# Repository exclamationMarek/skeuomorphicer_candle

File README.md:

# Skeuomorphicer Candle

A more skeuomorphic LED candle, one that you turn on with a flame, and off with a blow, like a real candle!
Super simple design with no microcontrollers, op-amps nor any other integrated circuits. Just one transistor, one thermistor and a couple of passives.

As seen on youtube, here: [https://www.youtube.com/watch?v=r8O8MNvkZiY](https://www.youtube.com/watch?v=r8O8MNvkZiY)

# How it works

* Heating the NTC thermistor makes its resistance drop, which increases the voltage on the MOSFET gate and turns on the bulb
* The current limiting R2 resistor gets hot
* The PCB is carefully designed to thermally connect R2 to the NTC
* Heat from R2 makes the NTC hot, so it stays hot even when the flame is removed
* This keeps the candle on
* Once you blow on the PCB, the heat is removed, breaking the cycle and turning off the light
* Yes, the schematic looks like a candle

* The current limiting (and heat producing) resistor is doubled, to surround the NTC on both sides
* They also share an electrical connection with the NTC - the VCC node (on top)
* That VCC copper connection is used to transfer heat from the resistors to the NTC
* But also, is wide and exposed to being blown at
* This is a finicky design challenge that required iterative fine tuning
* The current implementation works best with about 0.1W (total) dissipated on the heating resistors, which keeps the NTC at about 55°C
* Testd on a 1.0mm 2-layer PCB with 35um copper foil. Tested with black solder mask (it might make a difference?)

Note that this is the simplified schematic that omits the power supply. In real application, the varying voltage of batteries causes the circuit to be unreliable. With a full battery, the NTC runs too hot, making the candle difficult to blow out, and with a low battery it runs too cool, turning itself off unprompted. To fix this, the recommended design adds a voltage regulator (boost converter) to keep VCC stable and the candle reliable.

# PCB design available in 4 variants:
## [Minimal](Skeuomorphic_candle_minimal)
* Designed for 1.5V mini light bulb and 2xAA batteries
* Very low component count
* Does not work with LEDs!
* No ICs. Just 1 NMOS, 1 NTC and some resistors
* If you want the simplest skeuomorphicer candle, use this PCB.
* Alternatively, use with external 3.3V regulated supply

## [Basic - recommended](Skeuomorphic_candle_basic)
* Works great with a mini light bulb and OK-ish with LEDs
* Supports various batteries
* Low component count, but requires power regulator IC
* If you want to make a resonably well working skeuomorphicer candle, use this PCB

## [Custom](Skeuomorphic_candle_custom)
* PCB with extra footprints for implementation flexibility
* Can be configured as either the "Minimal" or "Basic" variant
* Can be configured as bulb + LEDs
* LED brightness can be adjusted, while maintaining reliable flame detection
* Has test points
* If you want to experiment with the design, use this PCB

## [Digital](Skeuomorphic_candle_digital)
* EWWWW digital microcontroller!
* 32bits?! For like one 'if' statement?!
* 2KB of RAM?! You can fly to the bloody moon on 2KB of RAM!
* If you're one of those futuristic cyberpunk chooms, use this PCB. I will try not to cry.

Detailed configuration and assembly instructions are in each PCB variant folder.

# License
This project is published under the [Creative Commons Attribution-NonCommercial 4.0 License](https://creativecommons.org/licenses/by-nc/4.0/deed.en)

Full text in license.txt

A commertial use license may be provided upon request

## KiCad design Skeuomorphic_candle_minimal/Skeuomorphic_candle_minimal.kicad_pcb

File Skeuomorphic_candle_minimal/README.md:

# Minimal Skeuomorphicer Candle
Does not work great, but uses very few parts

# UNTESTED!
As of releasing this repo, this PCB design is NOT TESTED. It might be all wrong.

# Part list (light bulb configuration)
* 1x 1.5V miniature tungsten bulb. Should draw about 100-130mA at 1.5V
* 1x SI2302 N-MOS (or similar)
* 1x 100k NTC in 0603 package
* 2x 33R resistors in 0603 package
* 1x 6.8k resistor in 0603 package
* 1x battery holder for 2xAA
* 2x AA battery (NiMH rechargable works great)

# Assembly manual (light bulb configuration)
* Populate all components as listed in the schematic
* Find a value of R1 that makes candle work well. REDUCE if hard to blow out, INCREASE if does not stay on
* Note that as the batteries are discharged, the threshold will shift, making it more likely that the candle does not stay on
* Therefore, tune R1 with full batteries, and make it so that it is barely possible to blow out the candle
* Supply from 2xAA batteries

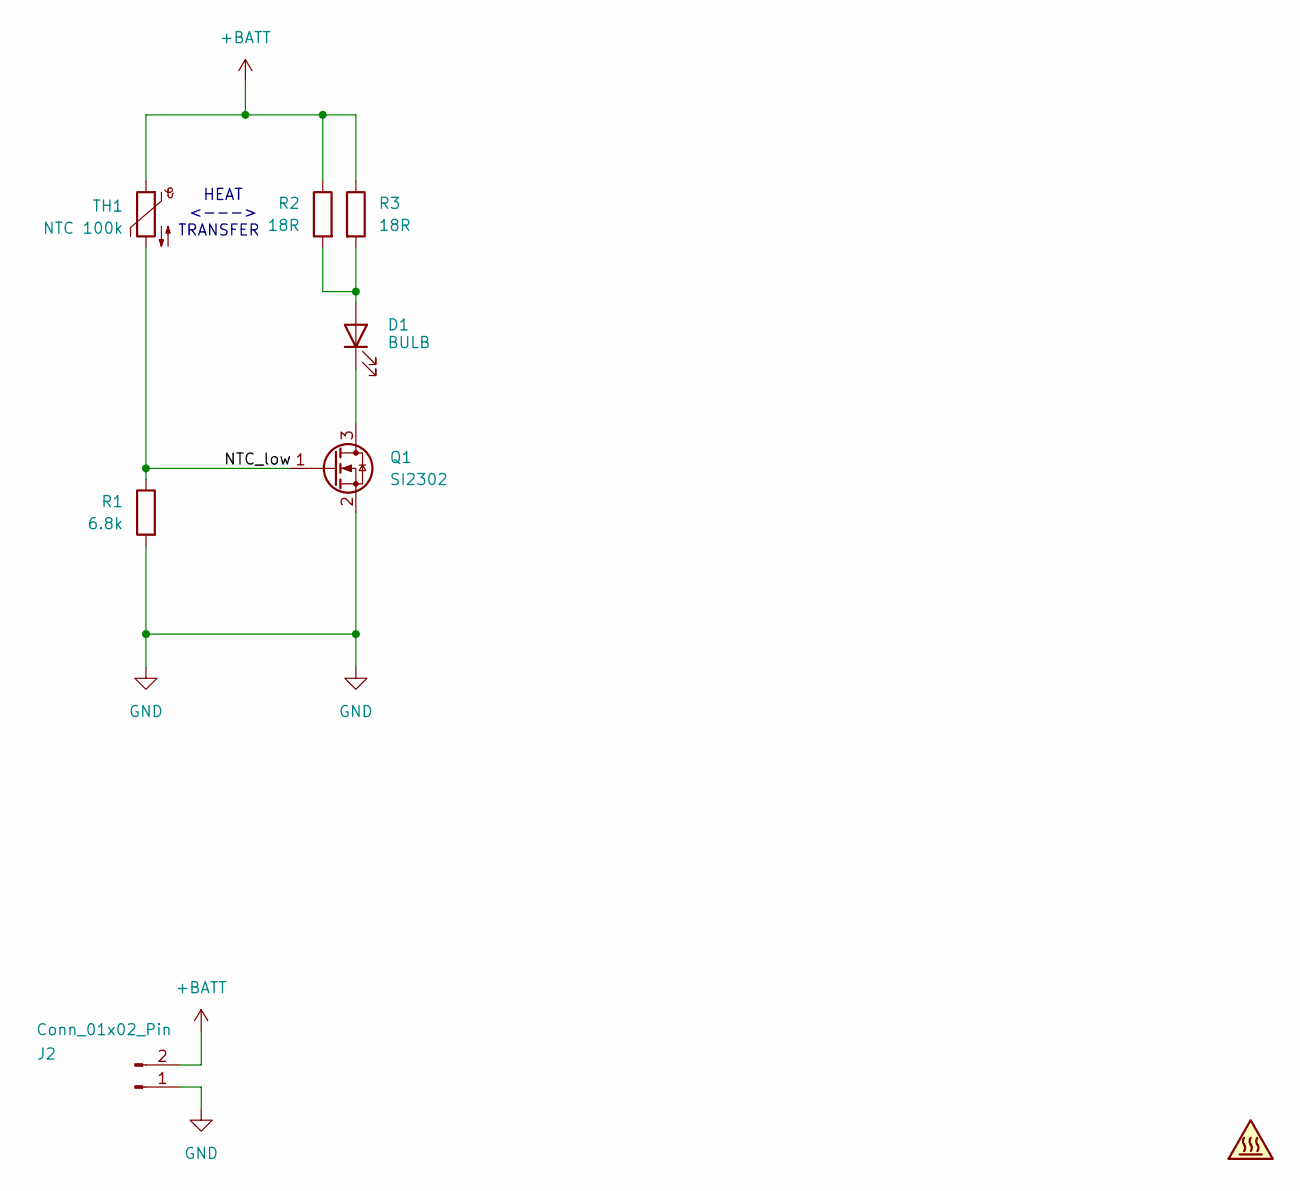
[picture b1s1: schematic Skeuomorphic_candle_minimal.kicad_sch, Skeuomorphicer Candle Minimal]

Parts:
D1: BULB; Mini_bulb_flat
J2: Conn_01x02_Pin; PinHeader_1x02_P2.54mm_Vertical
LOGO1: Logo; Skeuomorphicer_candle_logo
Q1: SI2302; SOT-23-handsoldering-smaller
R1: 6.8k; R_0603_1608Metric_Pad0.98x0.95mm_HandSolder
R2, R3: 18R; R_0603_1608Metric_Pad0.98x0.95mm_HandSolder
TH1: NTC 100k; R_0603_1608Metric_Pad0.98x0.95mm_HandSolder

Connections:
+BATT: J2.2, R2.1, R3.1, TH1.1
/NTC_low: Q1.1 (G), R1.1, TH1.2
GND: J2.1, Q1.2 (S), R1.2
unnamed: D1.2 (A), R2.2, R3.2
unnamed: D1.1 (K), Q1.3 (D)

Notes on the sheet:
HEAT <---> TRANSFER

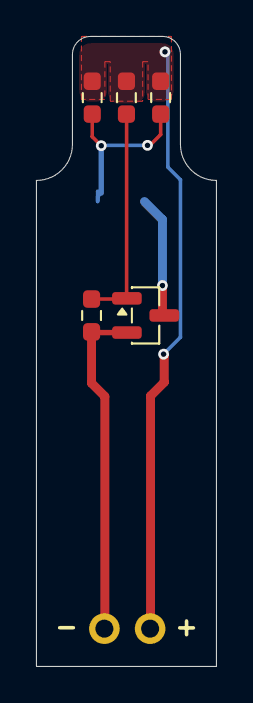
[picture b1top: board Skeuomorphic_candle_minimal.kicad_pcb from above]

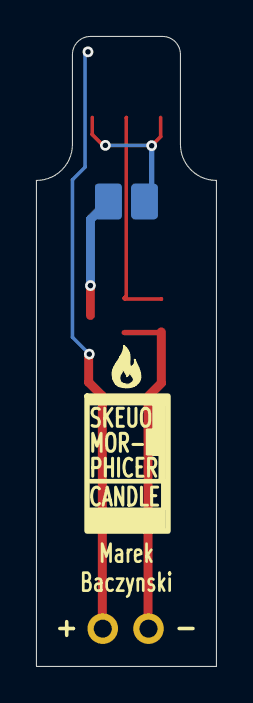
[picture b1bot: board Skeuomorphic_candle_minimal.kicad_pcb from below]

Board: 2 copper layers, 10.0 x 35.0 mm, 8 parts (2 on the bottom side), 5 nets.

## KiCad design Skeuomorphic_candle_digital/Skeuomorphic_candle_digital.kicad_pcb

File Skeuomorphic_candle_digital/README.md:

# Digital Skeuomorphicer Candle
For when you just have to put code into everything

# UNTESTED!
As of releasing this repo, this PCB design is NOT TESTED. It might be all wrong.

# Part list
* CH32V003J4M6 microcontroller in SOP-8 package
* 100k NTC in 0603
* SI2302 NMOS (or similar)
* 1uF capacitor in 0603 for the MCU
* 3V miniature tungsten bulb, or 2x 2835 LEDs
* Some 0603 resistors
* Optionally some 0603 LEDs
* 3xAA or 3xAAA battery holder or 1x LiPo battery

# Firmware
Firmware for the Digital Skeuomorphicer Candle is comming soon. Probably.

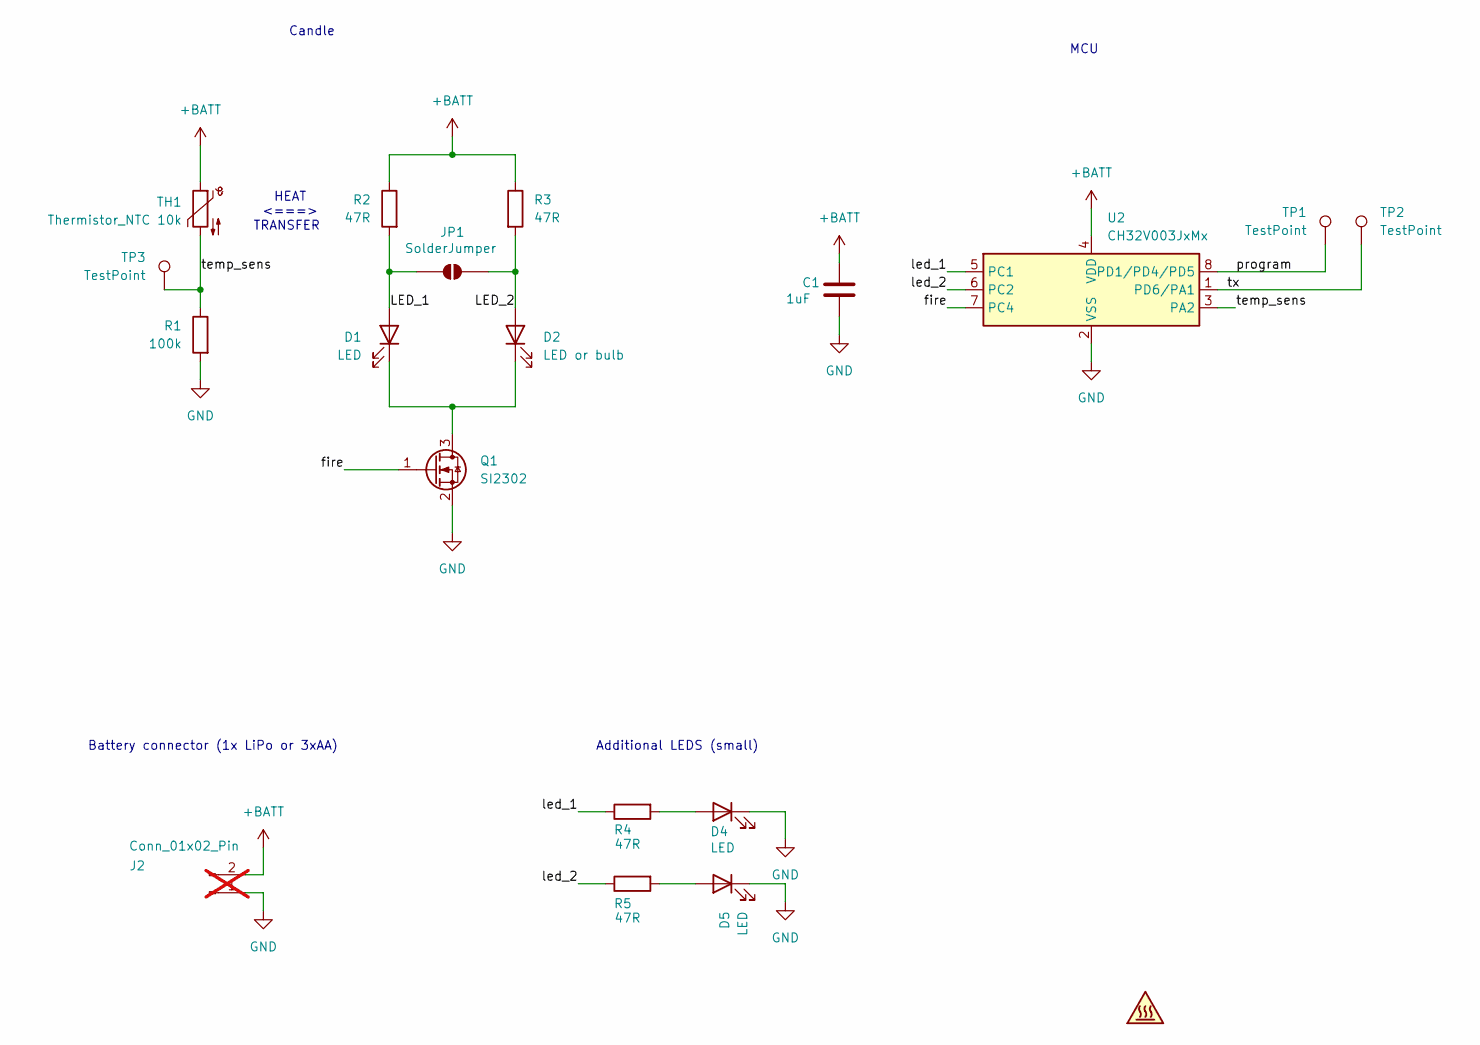
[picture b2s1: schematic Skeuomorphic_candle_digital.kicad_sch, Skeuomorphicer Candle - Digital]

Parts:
C1: 1uF; C_0603_1608Metric_Pad1.08x0.95mm_HandSolder
D1: LED; LED_PLCC_2835_Handsoldering
D2: LED or bulb; LED_PLCC_2835_Handsoldering
D4, D5: LED; LED_0603_1608Metric_Pad1.05x0.95mm_HandSolder
J2: Conn_01x02_Pin; PinHeader_1x02_P2.54mm_Vertical; not fitted
JP1: SolderJumper; SolderJumper-2_P1.3mm_Open_RoundedPad1.0x1.5mm
LOGO1: Logo; Skeuomorphicer_candle_logo
Q1: SI2302; SOT-23-handsoldering-smaller
R1: 100k; R_0603_1608Metric_Pad0.98x0.95mm_HandSolder
R2, R3, R4, R5: 47R; R_0603_1608Metric_Pad0.98x0.95mm_HandSolder
TH1: Thermistor_NTC 10k; R_0603_1608Metric_Pad0.98x0.95mm_HandSolder
TP1, TP2, TP3: TestPoint; TestPoint_Pad_D1.0mm
U2: CH32V003JxMx; JEITA_SOIC-8_3.9x4.9mm_P1.27mm

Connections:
+BATT: C1.1, J2.2, R2.1, R3.1, TH1.1, U2.4 (VDD)
/LED_1: D1.2 (A), JP1.1 (A), R2.2
/LED_2: D2.2 (A), JP1.2 (B), R3.2
/fire: Q1.1 (G), U2.7 (PC4)
/led_1: R4.1, U2.5 (PC1)
/led_2: R5.1, U2.6 (PC2)
/program: TP1.1 (1_1), U2.8 (PD1/PD4/PD5)
/temp_sens: R1.1, TH1.2, TP3.1 (1_1), U2.3 (PA2)
/tx: TP2.1 (1_1), U2.1 (PD6/PA1)
GND: C1.2, D4.1 (K), D5.1 (K), J2.1, Q1.2 (S), R1.2, U2.2 (VSS)
unnamed: D1.1 (K), D2.1 (K), Q1.3 (D)
unnamed: D4.2 (A), R4.2
unnamed: D5.2 (A), R5.2

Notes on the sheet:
MCU
Battery connector (1x LiPo or 3xAA)
HEAT <===> TRANSFER
Additional LEDS (small)
Candle

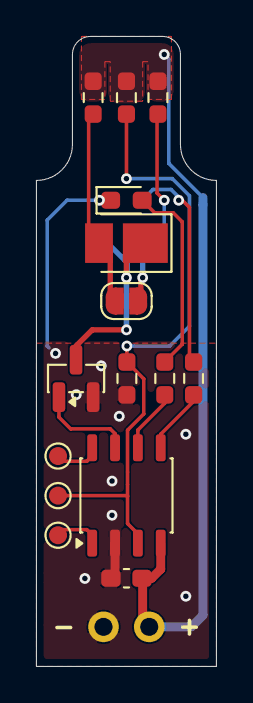
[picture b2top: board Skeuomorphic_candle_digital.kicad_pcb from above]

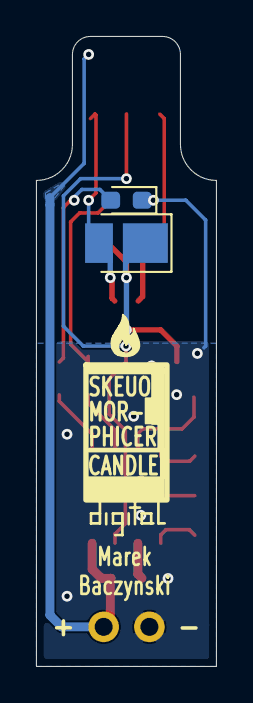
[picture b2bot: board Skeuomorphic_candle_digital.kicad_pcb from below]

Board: 2 copper layers, 10.0 x 35.0 mm, 19 parts (3 on the bottom side), 13 nets.

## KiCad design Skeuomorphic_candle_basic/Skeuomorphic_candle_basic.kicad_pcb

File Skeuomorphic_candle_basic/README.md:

# Basic Skeuomorphicer Candle
Most recommended design

# UNTESTED!
As of releasing this repo, this PCB design is NOT TESTED. It might be all wrong.

# Part list (light bulb configuration)
* 1x 1.5V miniature tungsten bulb. Should draw about 100-130mA at 1.5V
* 1x SI2302 N-MOS (or similar)
* 1x ETA1061V33 boost converter with 3.3V output
* 1x 2.2uH inductor in 1008 package
* 2x 4.7uF capacitors in 0603 package
* 1x 100k NTC in 0603 package
* 2x 33R resistors in 0603 package
* 1x 6.8k resistor in 0603 package
* 1x battery holder for 2xAA
* 2x AA battery (NiMH rechargable works great)

# Assembly manual (light bulb configuration)
* Bridge Jumper JP1
* Skip D1
* Place 1.5V bulb on D2
* Use 3v3 out regulator for U1
* Populate all other components as listed in the schematic
* Find a value of R1 that makes candle work well. REDUCE if hard to blow out, INCREASE if does not stay on
* Supply from 2xAA or 2xAAA batteries

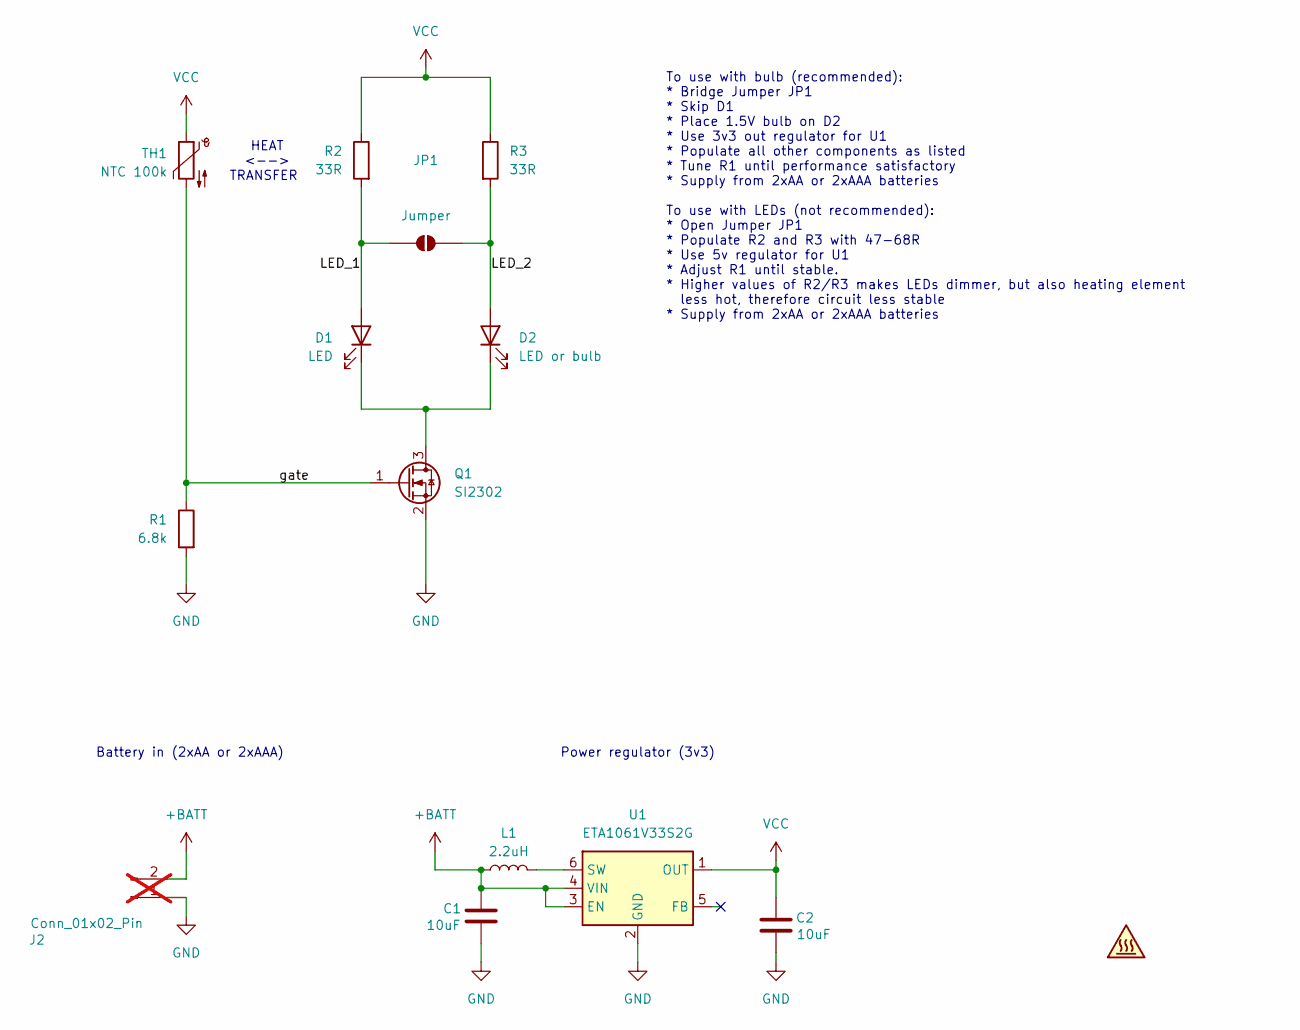
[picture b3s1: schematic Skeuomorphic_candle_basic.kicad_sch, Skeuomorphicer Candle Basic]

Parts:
C1, C2: 10uF; C_0603_1608Metric_Pad1.08x0.95mm_HandSolder
D1: LED; LED_PLCC_2835_Handsoldering
D2: LED or bulb; LED_PLCC_2835_Handsoldering
J2: Conn_01x02_Pin; PinHeader_1x02_P2.54mm_Vertical; not fitted
JP1: Jumper; SolderJumper-2_P1.3mm_Open_RoundedPad1.0x1.5mm
L1: 2.2uH; L_1008_2520Metric_Pad1.43x2.20mm_HandSolder; MPN WIP252012P-2R2ML
LOGO1: Logo; Skeuomorphicer_candle_logo
Q1: SI2302; SOT-23-handsoldering-smaller
R1: 6.8k; R_0603_1608Metric_Pad0.98x0.95mm_HandSolder
R2, R3: 33R; R_0603_1608Metric_Pad0.98x0.95mm_HandSolder
TH1: NTC 100k; R_0603_1608Metric_Pad0.98x0.95mm_HandSolder
U1: ETA1061V33S2G; SOT-23-6

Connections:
+BATT: C1.1, J2.2, L1.1, U1.3 (EN), U1.4 (VIN)
/LED_1: D1.2 (A), JP1.1 (A), R2.2
/LED_2: D2.2 (A), JP1.2 (B), R3.2
/gate: Q1.1 (G), R1.1, TH1.2
GND: C1.2, C2.2, J2.1, Q1.2 (S), R1.2, U1.2 (GND)
unnamed: D1.1 (K), D2.1 (K), Q1.3 (D)
unnamed: L1.2, U1.6 (SW)
VCC: C2.1, R2.1, R3.1, TH1.1, U1.1 (OUT)

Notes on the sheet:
To use with bulb (recommended): * Bridge Jumper JP1 * Skip D1 * Place 1.5V bulb on D2 * Use 3v3 out regulator for U1 * Populate all other components as listed * Tune R1 until performance satisfactory * Supply from 2xAA or 2xAAA batteries To use with LEDs (not recommended): * Open Jumper JP1 * Popul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
HEAT <--> TRANSFER
Battery in (2xAA or 2xAAA)
Power regulator (3v3)

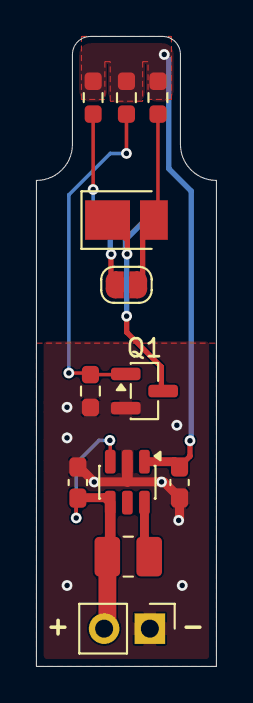
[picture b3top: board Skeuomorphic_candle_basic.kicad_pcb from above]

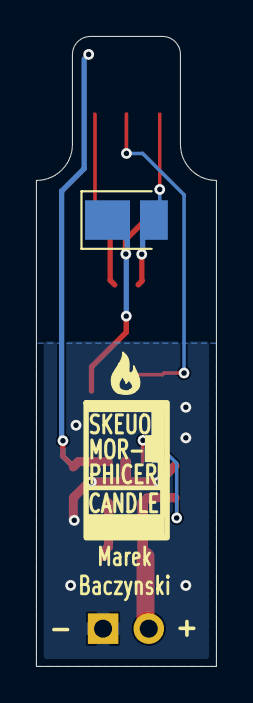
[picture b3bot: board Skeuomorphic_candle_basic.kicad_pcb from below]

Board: 2 copper layers, 10.0 x 35.0 mm, 14 parts (2 on the bottom side), 8 nets.

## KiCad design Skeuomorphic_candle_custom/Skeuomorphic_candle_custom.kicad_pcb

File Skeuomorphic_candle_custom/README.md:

# Custom Skeuomorphicer Candle
For when you want to experiment with the design

# UNTESTED!
As of releasing this repo, this PCB design is NOT TESTED. It might be all wrong.

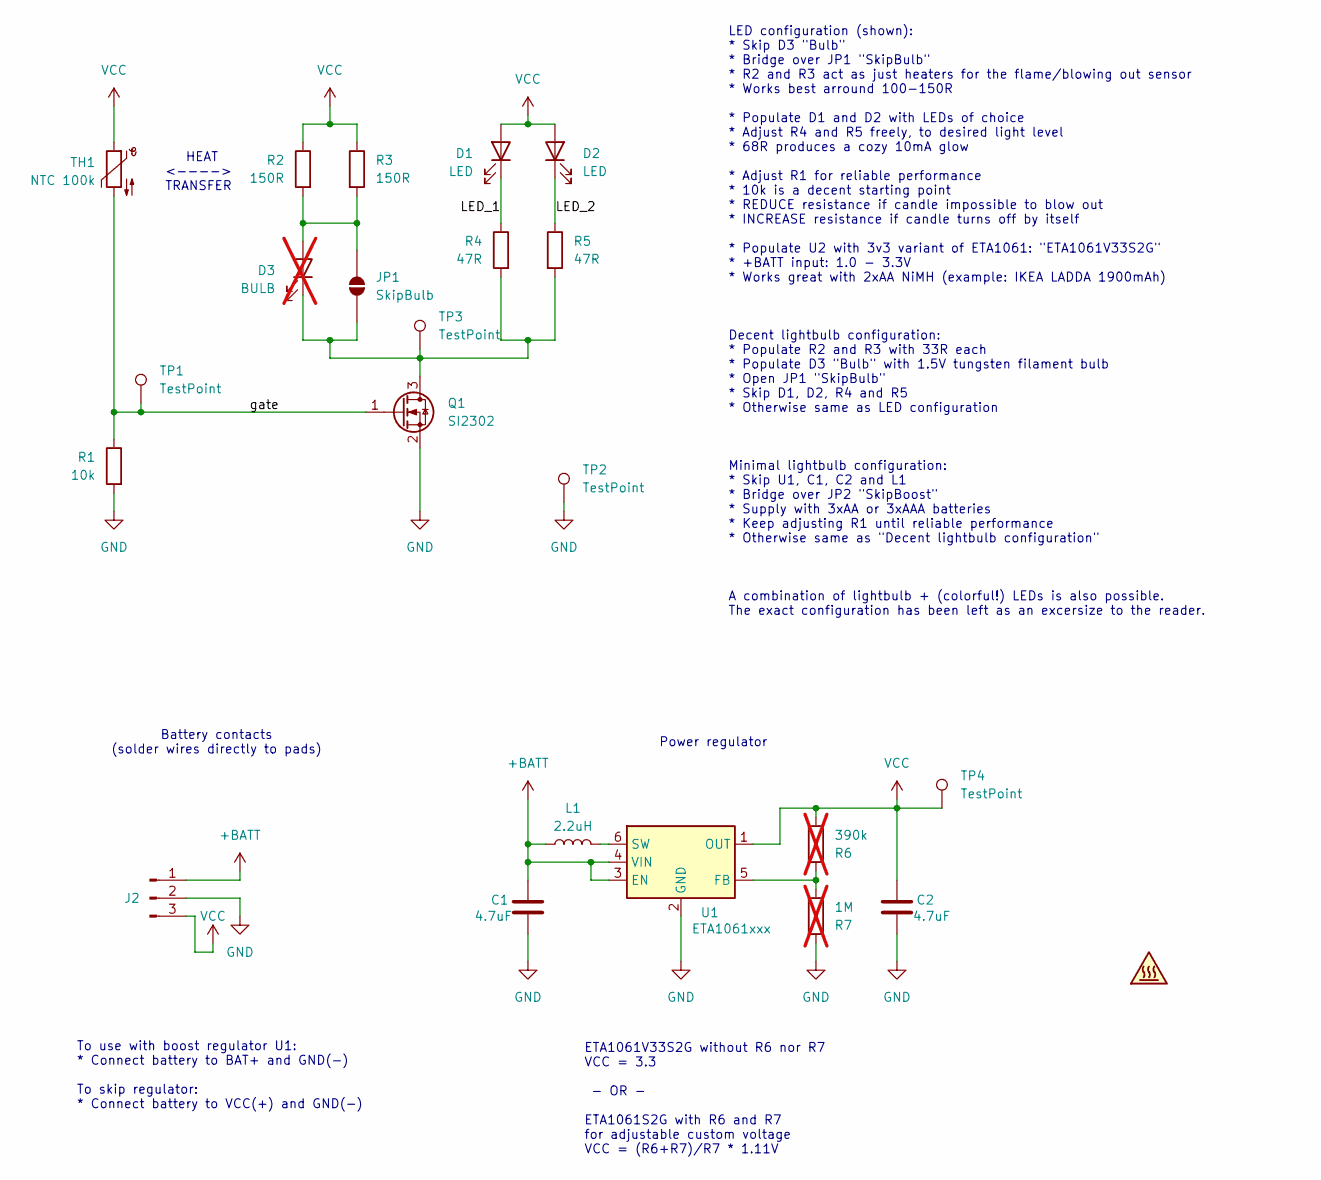
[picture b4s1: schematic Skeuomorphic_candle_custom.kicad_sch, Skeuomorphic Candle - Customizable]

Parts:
C1, C2: 4.7uF; C_0603_1608Metric_Pad1.08x0.95mm_HandSolder
D1, D2: LED; LED_PLCC_2835_Handsoldering
D3: BULB; Mini_bulb_flat; not fitted
J2: Conn_01x03_Pin; PinHeader_1x03_P2.54mm_Vertical
JP1: SkipBulb; SolderJumper-2_P1.3mm_Open_RoundedPad1.0x1.5mm
L1: 2.2uH; L_1008_2520Metric_Pad1.43x2.20mm_HandSolder; MPN INPAQ WIP252012P-2R2ML
LOGO1: Logo; Skeuomorphicer_candle_logo
Q1: SI2302; SOT-23-handsoldering-smaller
R1: 10k; R_0603_1608Metric_Pad0.98x0.95mm_HandSolder
R2, R3: 150R; R_0603_1608Metric_Pad0.98x0.95mm_HandSolder
R4, R5: 47R; R_0603_1608Metric_Pad0.98x0.95mm_HandSolder
R6: 390k; R_0603_1608Metric_Pad0.98x0.95mm_HandSolder; not fitted
R7: 1M; R_0603_1608Metric_Pad0.98x0.95mm_HandSolder; not fitted
TH1: NTC 100k; R_0603_1608Metric_Pad0.98x0.95mm_HandSolder
TP1, TP2, TP3, TP4: TestPoint; TestPoint_Pad_D1.0mm
U1: ETA1061xxx; SOT-23-6; MPN ETA1061V33S2G

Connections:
+BATT: C1.1, J2.1, L1.1, U1.3 (EN), U1.4 (VIN)
/LED_1: D1.1 (K), R4.1
/LED_2: D2.1 (K), R5.1
/gate: Q1.1 (G), R1.1, TH1.2, TP1.1 (1_1)
GND: C1.2, C2.2, J2.2, Q1.2 (S), R1.2, R7.1, TP2.1 (1_1), U1.2 (GND)
unnamed: D3.2 (A), JP1.2 (B), R2.2, R3.2
unnamed: D3.1 (K), JP1.1 (A), Q1.3 (D), R4.2, R5.2, TP3.1 (1_1)
unnamed: R6.1, R7.2, U1.5 (FB)
unnamed: L1.2, U1.6 (SW)
VCC: C2.1, D1.2 (A), D2.2 (A), J2.3, R2.1, R3.1, R6.2, TH1.1, TP4.1 (1_1), U1.1 (OUT)

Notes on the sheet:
Battery contacts (solder wires directly to pads)
To use with boost regulator U1: * Connect battery to BAT+ and GND(-) To skip regulator: * Connect battery to VCC(+) and GND(-)
Power regulator
ETA1061V33S2G without R6 nor R7 VCC = 3.3 - OR - ETA1061S2G with R6 and R7 for adjustable custom voltage VCC = (R6+R7)/R7 * 1.11V
LED configuration (shown): * Skip D3 "Bulb" * Bridge over JP1 "SkipBulb" * R2 and R3 act as just heaters for the flame/blowing out sensor * Works best arround 100-150R * Populate D1 and D2 with LEDs of choice * Adjust R4 and R5 freely, to desired light level * 68R produces a cozy 10mA glow * Adjust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
HEAT <----> TRANSFER

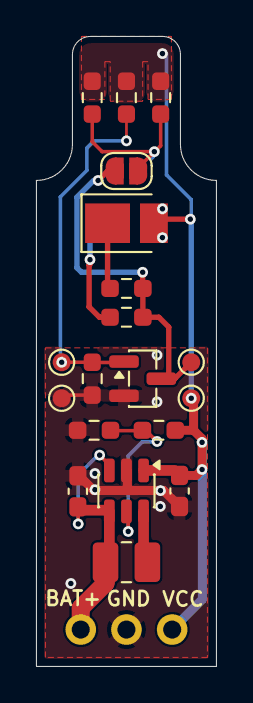
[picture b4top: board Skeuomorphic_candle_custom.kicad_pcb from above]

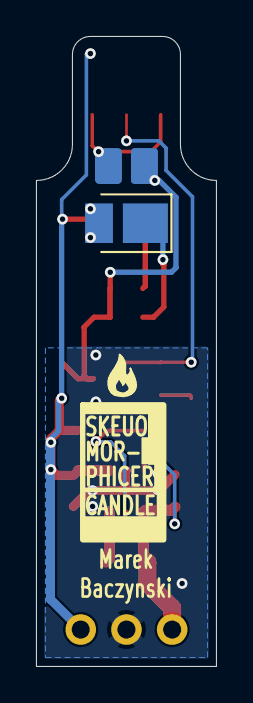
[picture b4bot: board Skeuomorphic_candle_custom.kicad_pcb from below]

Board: 2 copper layers, 10.0 x 35.0 mm, 23 parts (3 on the bottom side), 10 nets.
